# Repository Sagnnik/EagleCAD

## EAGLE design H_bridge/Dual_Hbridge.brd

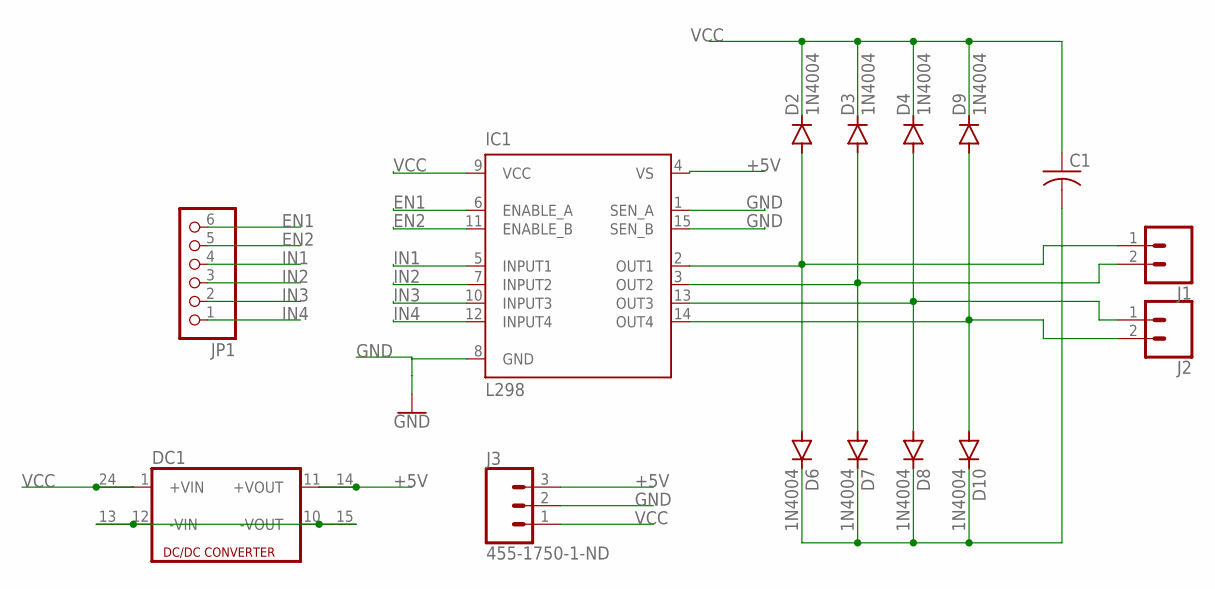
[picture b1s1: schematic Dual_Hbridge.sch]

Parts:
C1: C-US025-024X044; C025-024X044
D2, D3, D4, D6, D7, D8, D9, D10: 1N4004; DO41-10
DC1: DC213R; CMK
IC1: L298; MULTIWATT-15
J1, J2: CONN_02; 1X02
J3: 455-1750-1-ND; 1X03
JP1: PINHD-1X6; 1X06

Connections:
+5V: DC1.11 (+VOUT), DC1.14 (+VOUT1), IC1.4 (VS), J3.3
EN1: IC1.6 (ENABLE_A), JP1.6
EN2: IC1.11 (ENABLE_B), JP1.5
GND: IC1.1 (SEN_A), IC1.8 (GND), IC1.15 (SEN_B), J3.2
IN1: IC1.5 (INPUT1), JP1.4
IN2: IC1.7 (INPUT2), JP1.3
IN3: IC1.10 (INPUT3), JP1.2
IN4: IC1.12 (INPUT4), JP1.1
unnamed: C1.2, D6.C, D7.C, D8.C, D10.C
unnamed: D2.A, D6.A, IC1.2 (OUT1), J1.1
unnamed: D3.A, D7.A, IC1.3 (OUT2), J1.2
unnamed: D4.A, D8.A, IC1.13 (OUT3), J2.1
unnamed: D9.A, D10.A, IC1.14 (OUT4), J2.2
unnamed: DC1.10 (-VOUT), DC1.12 (-VIN), DC1.13 (-VIN1), DC1.15 (-VOUT1)
VCC: C1.1, D2.C, D3.C, D4.C, D9.C, DC1.1 (+VIN), DC1.24 (+VIN1), IC1.9 (VCC), J3.1

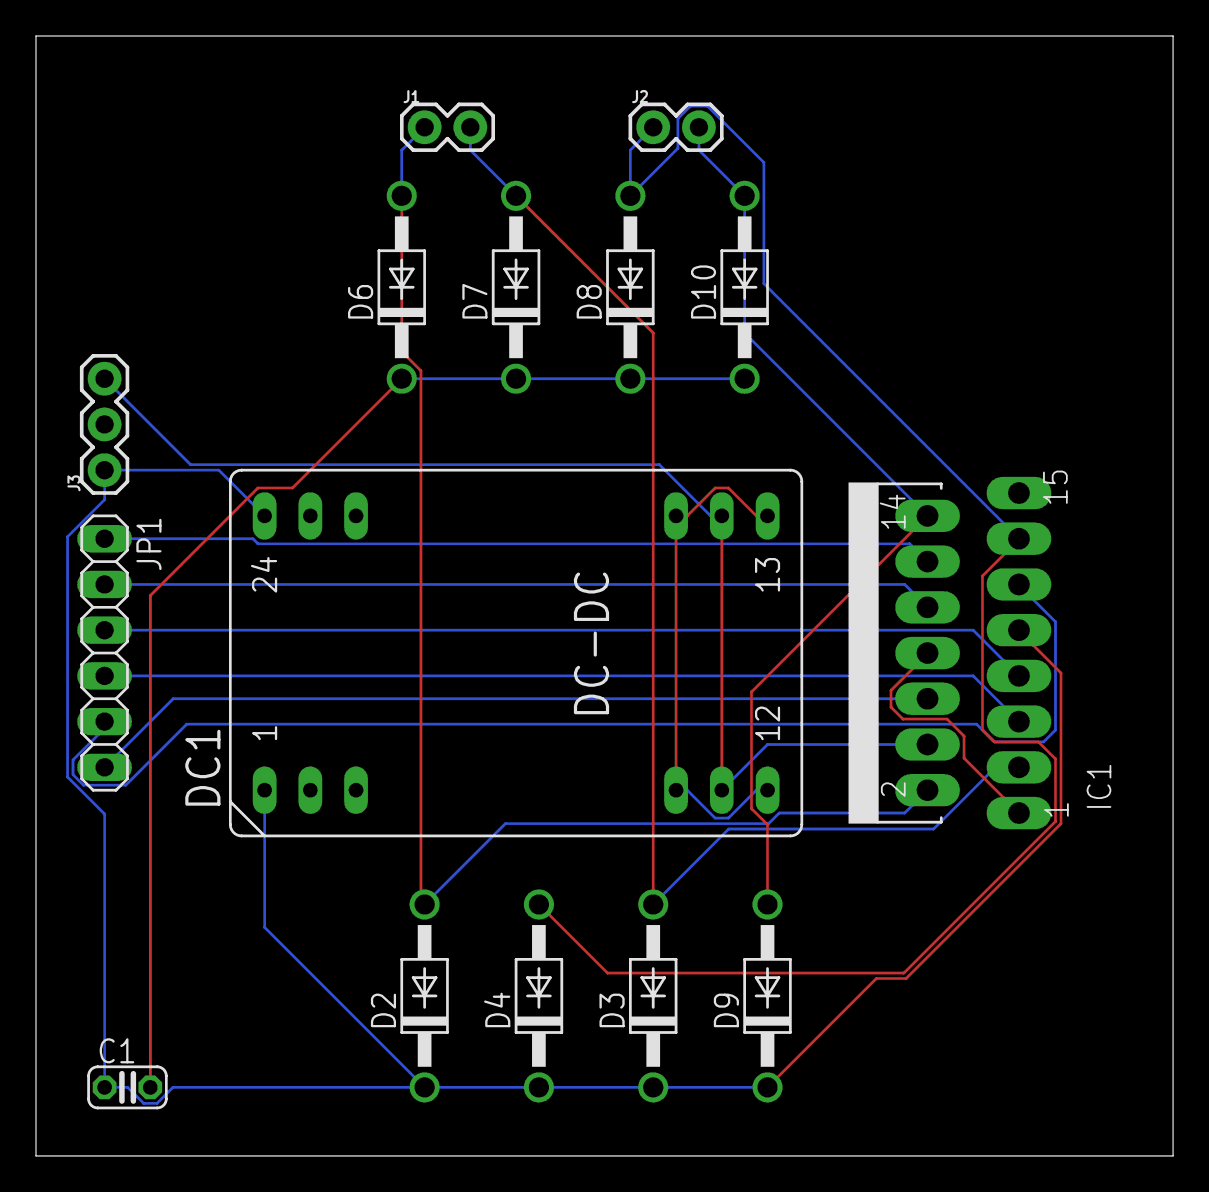
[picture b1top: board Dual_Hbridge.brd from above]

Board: 2 copper layers, 63.2 x 62.2 mm, 15 parts (0 on the bottom side), 15 nets.

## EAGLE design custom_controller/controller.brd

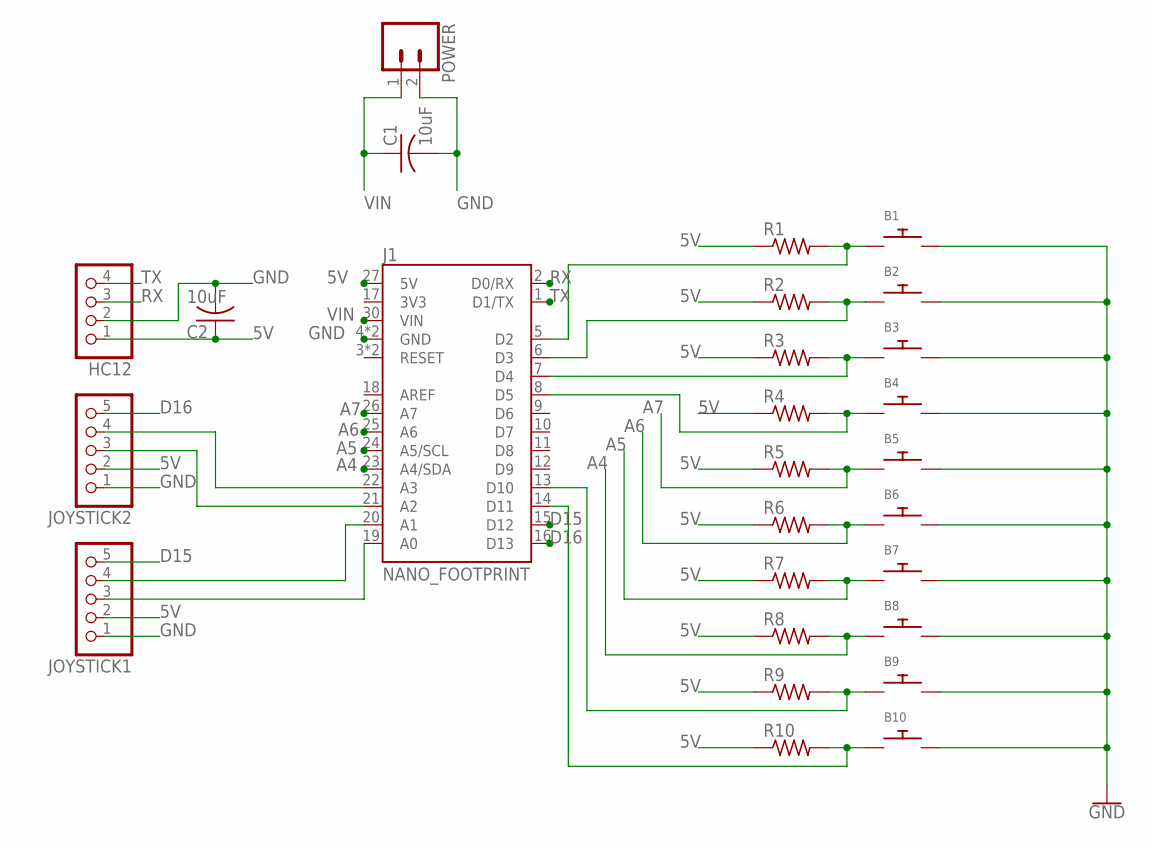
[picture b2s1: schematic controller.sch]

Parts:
B1, B2, B3, B4, B5, B6, B7, B8, B9, B10: SWITCH_PUSHBUTTONEVQ-PE; TACT_PANA-EVQ
C1, C2: 10uF; C025-024X044
HC12: PINHD-1X4; 1X04
J1: NANO_FOOTPRINT; NANO
JOYSTICK1, JOYSTICK2: PINHD-1X5; 1X05
POWER: CONN_02; 1X02
R1, R2, R3, R4, R5, R6, R7, R8, R9, R10: R-US_0204/7; 0204/7

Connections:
5V: C2.1, HC12.1, J1.27 (5V), JOYSTICK1.2, JOYSTICK2.2, R1.1, R2.1, R3.1, R4.1, R5.1, R6.1, R7.1, R8.1, R9.1, R10.1
A4: B8.P$1, J1.23 (A4/SDA), R8.2
A5: B7.P$1, J1.24 (A5/SCL), R7.2
A6: B6.P$1, J1.25 (A6), R6.2
A7: B5.P$1, J1.26 (A7), R5.2
D15: J1.15 (D12), JOYSTICK1.5
D16: J1.16 (D13), JOYSTICK2.5
GND: B1.P$2, B2.P$2, B3.P$2, B4.P$2, B5.P$2, B6.P$2, B7.P$2, B8.P$2, B9.P$2, B10.P$2, C1.2, C2.2, HC12.2, J1.4 (GND), J1.29 (GND), JOYSTICK1.1, JOYSTICK2.1, POWER.2
unnamed: B1.P$1, J1.5 (D2), R1.2
unnamed: B2.P$1, J1.6 (D3), R2.2
unnamed: B3.P$1, J1.7 (D4), R3.2
unnamed: B4.P$1, J1.8 (D5), R4.2
unnamed: J1.19 (A0), JOYSTICK1.3
unnamed: J1.20 (A1), JOYSTICK1.4
unnamed: J1.21 (A2), JOYSTICK2.3
unnamed: B9.P$1, J1.13 (D10), R9.2
unnamed: B10.P$1, J1.14 (D11), R10.2
unnamed: J1.22 (A3), JOYSTICK2.4
RX: HC12.3, J1.2 (D0/RX)
TX: HC12.4, J1.1 (D1/TX)
VIN: C1.1, J1.30 (VIN), POWER.1

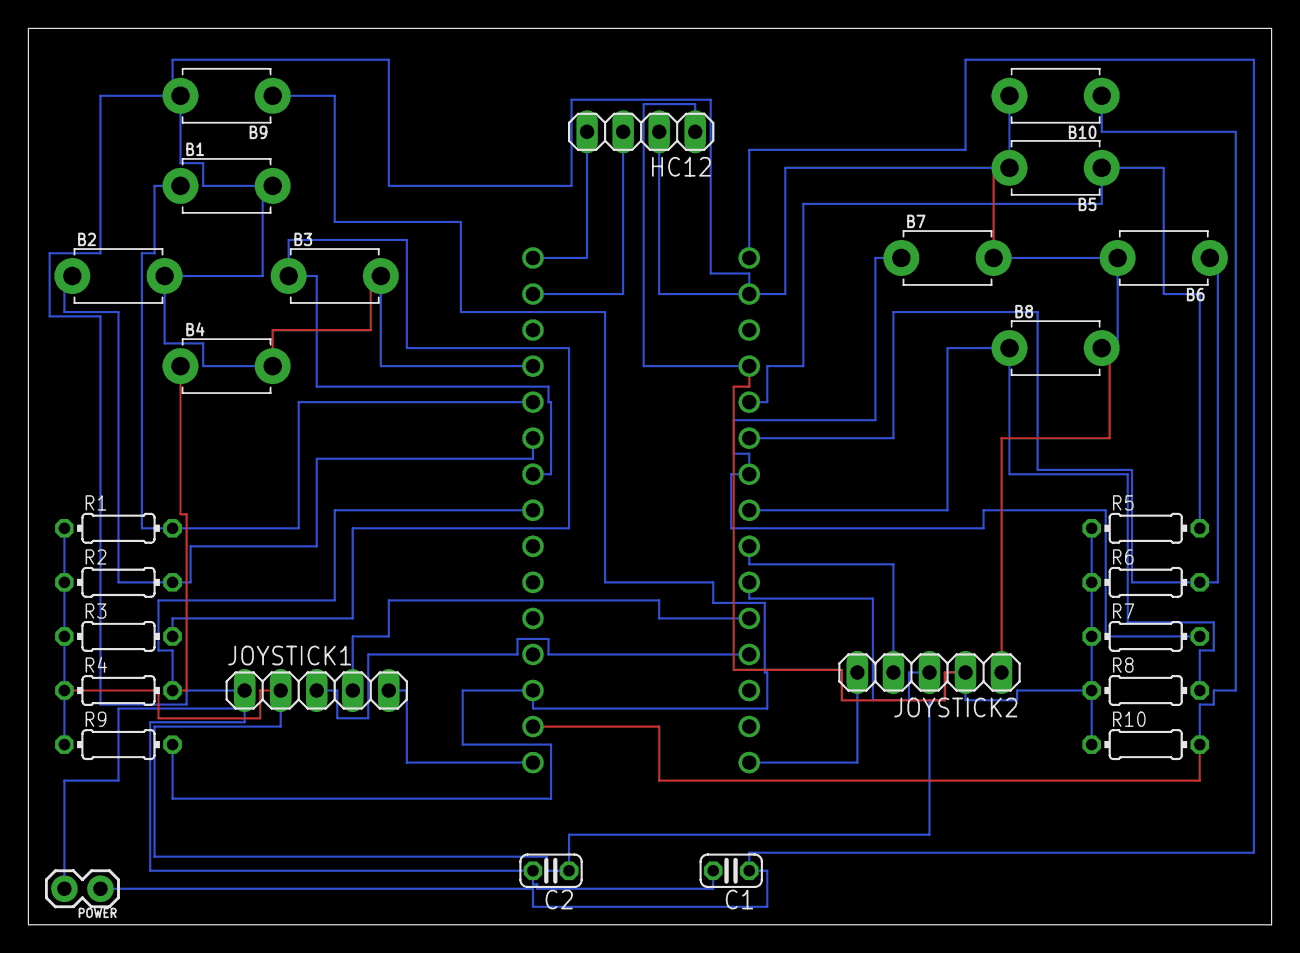
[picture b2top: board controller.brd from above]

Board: 2 copper layers, 87.6 x 63.2 mm, 27 parts (0 on the bottom side), 21 nets.

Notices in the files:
parts and their libraries:
SparkFun-Connectors: Licensing: Creative Commons ShareAlike 4.0 International - https://creativecommons.org/licenses/by-sa/4.0
